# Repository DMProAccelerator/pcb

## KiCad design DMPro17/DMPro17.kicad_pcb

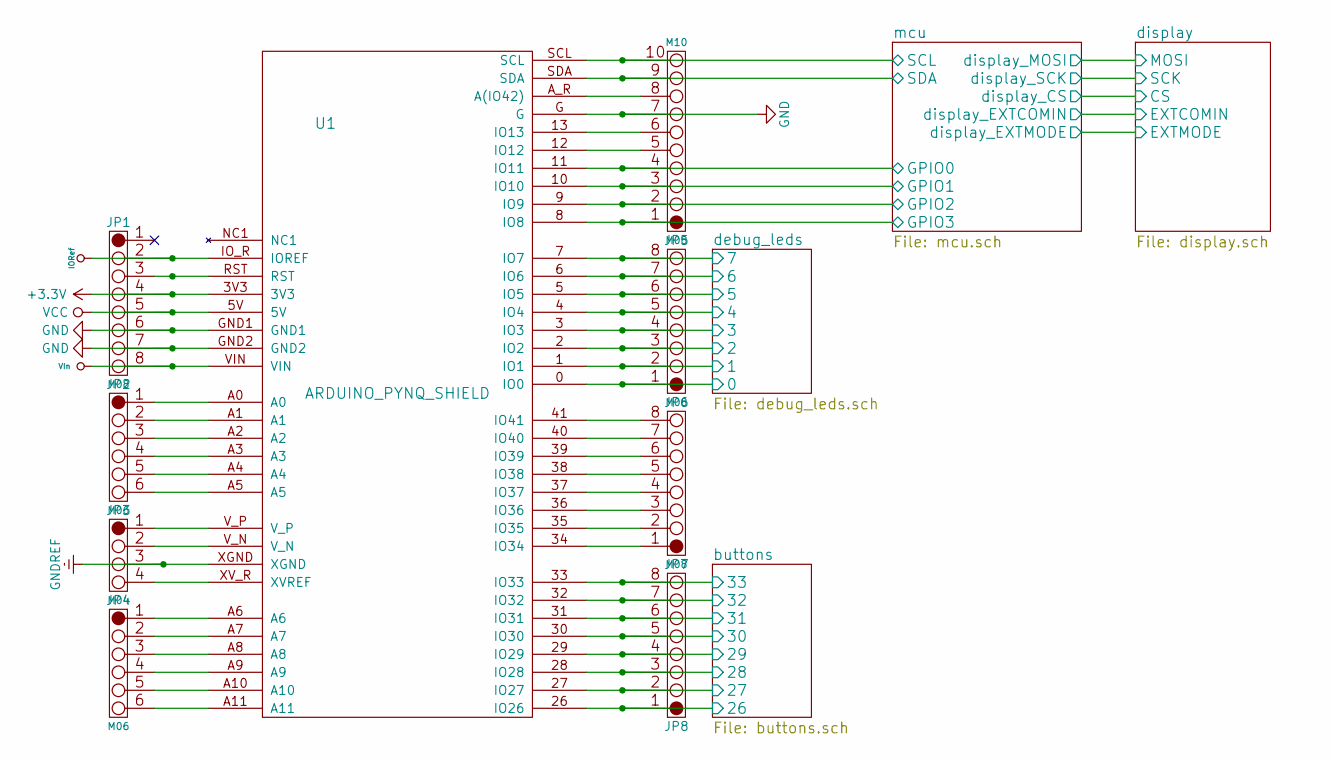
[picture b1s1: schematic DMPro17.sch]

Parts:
JP1, JP6, JP7, JP8: M08; 1X08
JP2, JP4: M06; 1X06
JP3: M04; 1X04
JP5: M10; 1X10
U1: ARDUINO_PYNQ_SHIELD

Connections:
+3V3: JP1.4, U1.3V3; also elsewhere on the board
/buttons/26: JP8.1, U1.26 (IO26); also elsewhere on the board
/buttons/27: JP8.2, U1.27 (IO27); also elsewhere on the board
/buttons/28: JP8.3, U1.28 (IO28); also elsewhere on the board
/buttons/29: JP8.4, U1.29 (IO29); also elsewhere on the board
/buttons/30: JP8.5, U1.30 (IO30); also elsewhere on the board
/buttons/31: JP8.6, U1.31 (IO31); also elsewhere on the board
/buttons/32: JP8.7, U1.32 (IO32); also elsewhere on the board
/buttons/33: JP8.8, U1.33 (IO33); also elsewhere on the board
/debug_leds/0: JP6.1, U1.0 (IO0); also elsewhere on the board
/debug_leds/1: JP6.2, U1.1 (IO1); also elsewhere on the board
/debug_leds/2: JP6.3, U1.2 (IO2); also elsewhere on the board
/debug_leds/3: JP6.4, U1.3 (IO3); also elsewhere on the board
/debug_leds/4: JP6.5, U1.4 (IO4); also elsewhere on the board
/debug_leds/5: JP6.6, U1.5 (IO5); also elsewhere on the board
/debug_leds/6: JP6.7, U1.6 (IO6); also elsewhere on the board
/debug_leds/7: JP6.8, U1.7 (IO7); also elsewhere on the board
/mcu/GPIO0: JP5.4, U1.11 (IO11); also elsewhere on the board
/mcu/GPIO1: JP5.3, U1.10 (IO10); also elsewhere on the board
/mcu/GPIO2: JP5.2, U1.9 (IO9); also elsewhere on the board
/mcu/GPIO3: JP5.1, U1.8 (IO8); also elsewhere on the board
/mcu/SCL: JP5.10, U1.SCL; also elsewhere on the board
/mcu/SDA: JP5.9, U1.SDA; also elsewhere on the board
GND: JP1.6, JP1.7, JP5.7, U1.G, U1.GND1, U1.GND2; also elsewhere on the board
GNDREF: JP3.3, U1.XGND
IORef: JP1.2, U1.IO_R (IOREF)
unnamed: JP1.3, U1.RST
unnamed: JP2.1, U1.A0
unnamed: JP2.2, U1.A1
unnamed: JP2.3, U1.A2
unnamed: JP2.4, U1.A3
unnamed: JP2.5, U1.A4
unnamed: JP2.6, U1.A5
unnamed: JP3.1, U1.V_P
unnamed: JP3.2, U1.V_N
unnamed: JP3.4, U1.XV_R (XVREF)
unnamed: JP4.1, U1.A6
unnamed: JP4.2, U1.A7
unnamed: JP4.3, U1.A8
unnamed: JP4.4, U1.A9
unnamed: JP4.5, U1.A10
unnamed: JP4.6, U1.A11
unnamed: JP5.5, U1.12 (IO12)
unnamed: JP5.6, U1.13 (IO13)
unnamed: JP5.8, U1.A_R (A(IO42))
unnamed: JP7.1, U1.34 (IO34)
unnamed: JP7.2, U1.35 (IO35)
unnamed: JP7.3, U1.36 (IO36)
unnamed: JP7.4, U1.37 (IO37)
unnamed: JP7.5, U1.38 (IO38)
unnamed: JP7.6, U1.39 (IO39)
unnamed: JP7.7, U1.40 (IO40)
unnamed: JP7.8, U1.41 (IO41)
VCC: JP1.5, U1.5V
VIn: JP1.8, U1.VIN

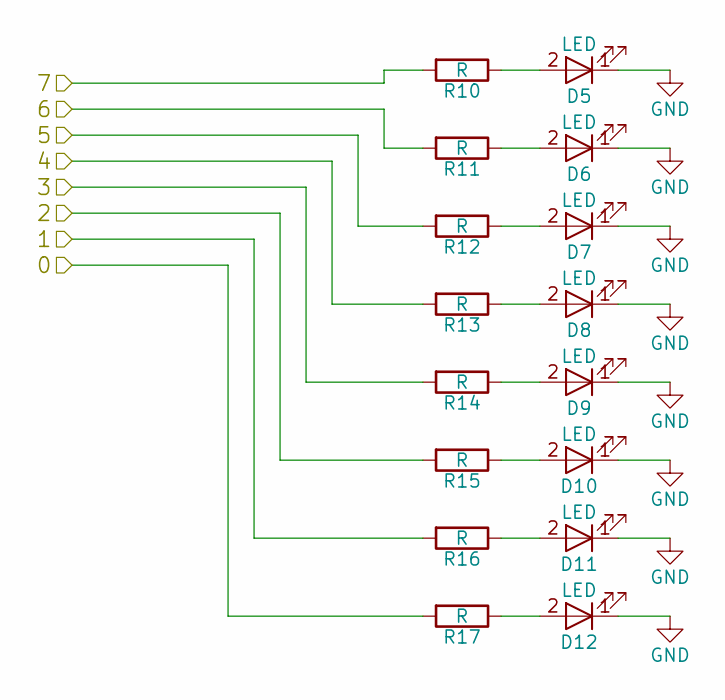
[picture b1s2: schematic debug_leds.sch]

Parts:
D5, D6, D7, D8, D9, D10, D11, D12: LED; LED_0603
R10, R11, R12, R13, R14, R15, R16, R17: R; R_0603

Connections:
/debug_leds/0: R17.2; also elsewhere on the board
/debug_leds/1: R16.2; also elsewhere on the board
/debug_leds/2: R15.2; also elsewhere on the board
/debug_leds/3: R14.2; also elsewhere on the board
/debug_leds/4: R13.2; also elsewhere on the board
/debug_leds/5: R12.2; also elsewhere on the board
/debug_leds/6: R11.2; also elsewhere on the board
/debug_leds/7: R10.2; also elsewhere on the board
GND: D5.1 (K), D6.1 (K), D7.1 (K), D8.1 (K), D9.1 (K), D10.1 (K), D11.1 (K), D12.1 (K); also elsewhere on the board
unnamed: D5.2 (A), R10.1
unnamed: D6.2 (A), R11.1
unnamed: D7.2 (A), R12.1
unnamed: D8.2 (A), R13.1
unnamed: D9.2 (A), R14.1
unnamed: D10.2 (A), R15.1
unnamed: D11.2 (A), R16.1
unnamed: D12.2 (A), R17.1

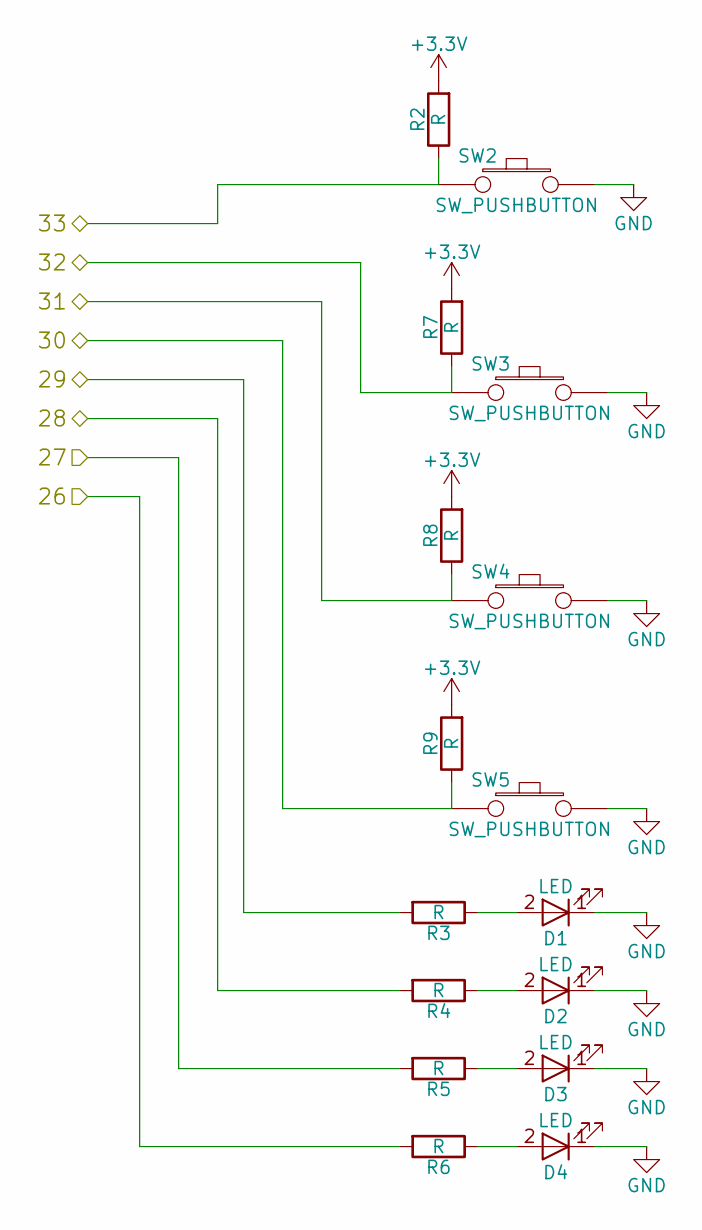
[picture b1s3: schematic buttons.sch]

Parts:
D1, D2, D3, D4: LED; LED_0603
R2, R3, R4, R5, R6, R7, R8, R9: R; R_0603
SW2, SW3, SW4, SW5: SW_PUSHBUTTON; SW_PUSHBUTTON_SMD

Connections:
+3V3: R2.2, R7.2, R8.2, R9.2; also elsewhere on the board
/buttons/26: R6.2; also elsewhere on the board
/buttons/27: R5.2; also elsewhere on the board
/buttons/28: R4.2; also elsewhere on the board
/buttons/29: R3.2; also elsewhere on the board
/buttons/30: R9.1, SW5.1; also elsewhere on the board
/buttons/31: R8.1, SW4.1; also elsewhere on the board
/buttons/32: R7.1, SW3.1; also elsewhere on the board
/buttons/33: R2.1, SW2.1; also elsewhere on the board
GND: D1.1 (K), D2.1 (K), D3.1 (K), D4.1 (K), SW2.2, SW3.2, SW4.2, SW5.2; also elsewhere on the board
unnamed: D1.2 (A), R3.1
unnamed: D2.2 (A), R4.1
unnamed: D3.2 (A), R5.1
unnamed: D4.2 (A), R6.1

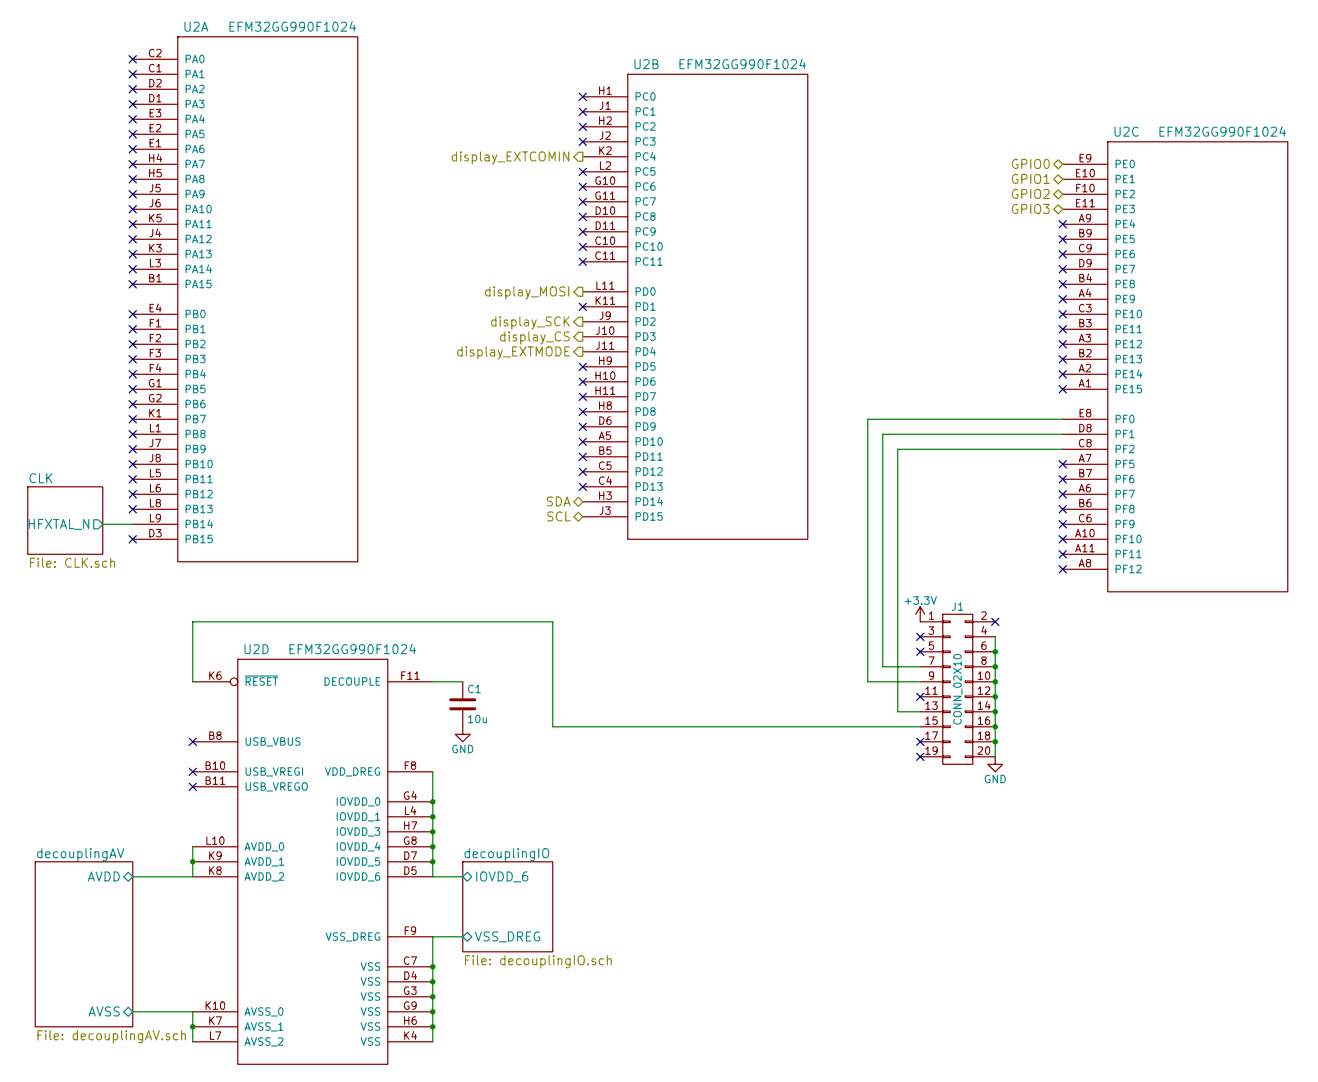
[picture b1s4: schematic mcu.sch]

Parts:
C1: 10u; C_0603
J1: CONN_02X10; Multicomp_MC9A12-2034_2x10x2.54mm_Straight
U2: EFM32GG990F1024; EFM32_BGA112

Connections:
+3V3: J1.1, U2.D5 (IOVDD_6), U2.D7 (IOVDD_5), U2.F8 (VDD_DREG), U2.G4 (IOVDD_0), U2.G8 (IOVDD_4), U2.H7 (IOVDD_3), U2.L4 (IOVDD_1); also elsewhere on the board
/display/CS: U2.J10 (PD3); also elsewhere on the board
/display/EXTCOMIN: U2.K2 (PC4); also elsewhere on the board
/display/EXTMODE: U2.J11 (PD4); also elsewhere on the board
/display/MOSI: U2.L11 (PD0); also elsewhere on the board
/display/SCK: U2.J9 (PD2); also elsewhere on the board
/mcu/CLK/HFXTAL_N: U2.L9 (PB14); also elsewhere on the board
/mcu/GPIO0: U2.E9 (PE0); also elsewhere on the board
/mcu/GPIO1: U2.E10 (PE1); also elsewhere on the board
/mcu/GPIO2: U2.F10 (PE2); also elsewhere on the board
/mcu/GPIO3: U2.E11 (PE3); also elsewhere on the board
/mcu/SCL: U2.J3 (PD15); also elsewhere on the board
/mcu/SDA: U2.H3 (PD14); also elsewhere on the board
/mcu/decouplingAV/AVDD: U2.K8 (AVDD_2), U2.K9 (AVDD_1), U2.L10 (AVDD_0); also elsewhere on the board
GND: C1.2, J1.4, J1.6, J1.8, J1.10, J1.12, J1.14, J1.16, J1.18, J1.20, U2.C7 (VSS), U2.D4 (VSS), U2.F9 (VSS_DREG), U2.G3 (VSS), U2.G9 (VSS), U2.H6 (VSS), U2.K4 (VSS), U2.K7 (AVSS_1), U2.K10 (AVSS_0), U2.L7 (AVSS_2); also elsewhere on the board
unnamed: C1.1, U2.F11 (DECOUPLE)
unnamed: J1.7, U2.D8 (PF1)
unnamed: J1.9, U2.E8 (PF0)
unnamed: J1.13, U2.C8 (PF2)
unnamed: J1.15, U2.K6 (~RESET~)

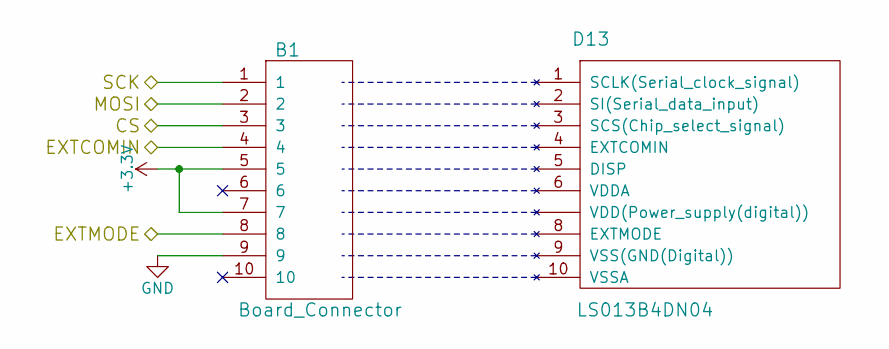
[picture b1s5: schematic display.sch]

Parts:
B1: Board_Connector
D13: LS013B4DN04

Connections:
+3V3: B1.5, B1.7; also elsewhere on the board
/display/CS: B1.3; also elsewhere on the board
/display/EXTCOMIN: B1.4; also elsewhere on the board
/display/EXTMODE: B1.8; also elsewhere on the board
/display/MOSI: B1.2; also elsewhere on the board
/display/SCK: B1.1; also elsewhere on the board
GND: B1.9; also elsewhere on the board

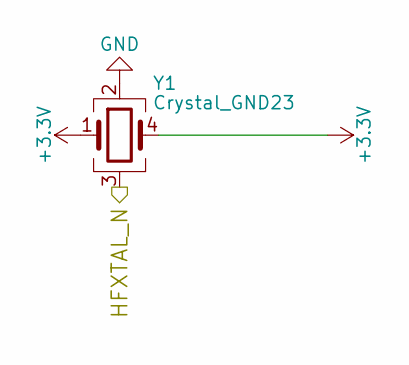
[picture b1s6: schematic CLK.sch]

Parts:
Y1: Crystal_GND23; Crystal_SMD_3225-4pin_3.2x2.5mm

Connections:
+3V3: Y1.1, Y1.4; also elsewhere on the board
/mcu/CLK/HFXTAL_N: Y1.3; also elsewhere on the board
GND: Y1.2; also elsewhere on the board

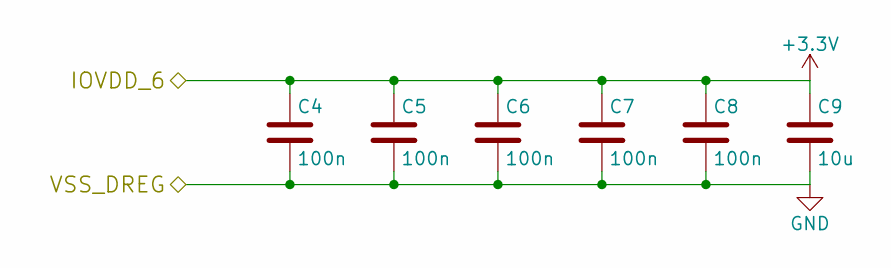
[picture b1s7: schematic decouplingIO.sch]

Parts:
C4, C5, C6, C7, C8: 100n; C_0603
C9: 10u; C_0603

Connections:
+3V3: C4.1, C5.1, C6.1, C7.1, C8.1, C9.1; also elsewhere on the board
GND: C4.2, C5.2, C6.2, C7.2, C8.2, C9.2; also elsewhere on the board

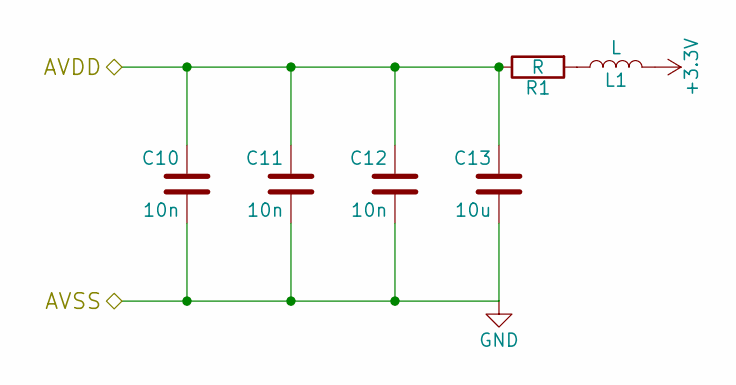
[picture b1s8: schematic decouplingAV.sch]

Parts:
C10, C11, C12: 10n; C_0603
C13: 10u; C_0603
L1: L; L_0603
R1: R; R_0603

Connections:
+3V3: L1.1; also elsewhere on the board
/mcu/decouplingAV/AVDD: C10.1, C11.1, C12.1, C13.1, R1.1; also elsewhere on the board
GND: C10.2, C11.2, C12.2, C13.2; also elsewhere on the board
unnamed: L1.2, R1.2

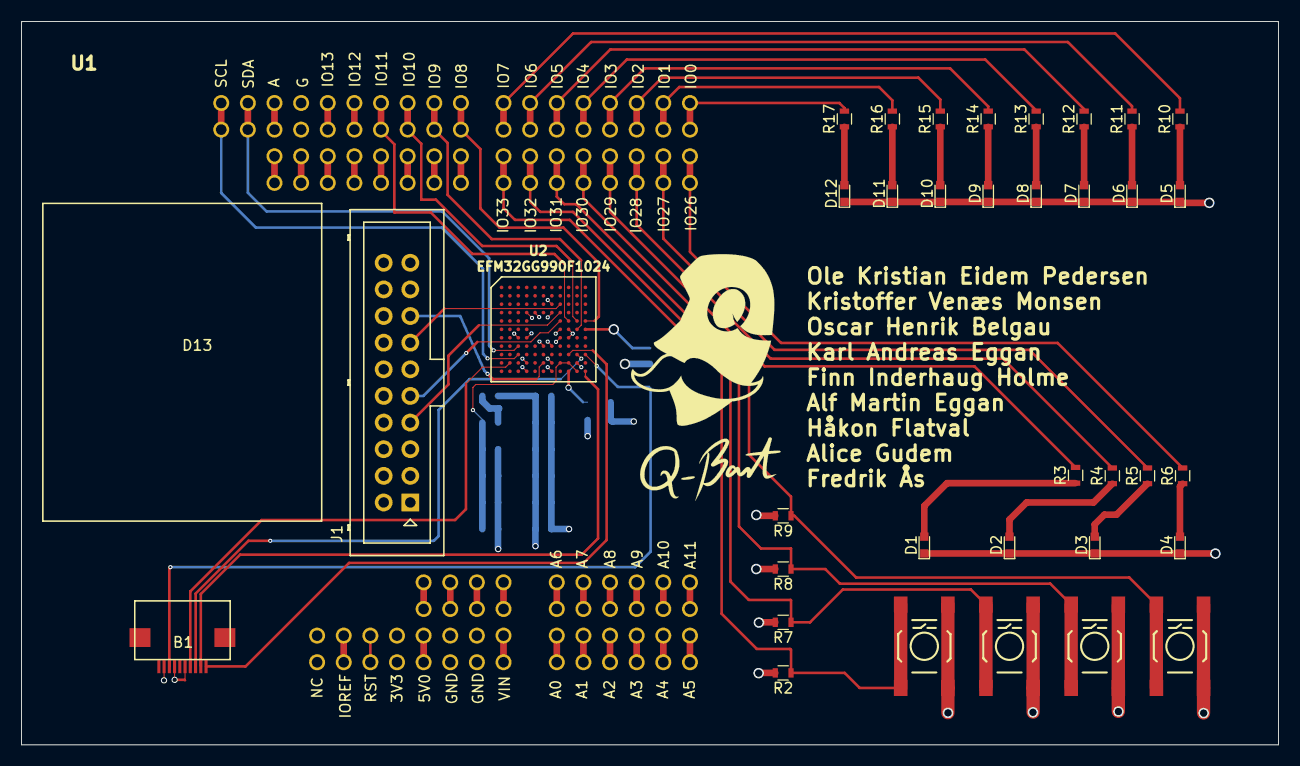
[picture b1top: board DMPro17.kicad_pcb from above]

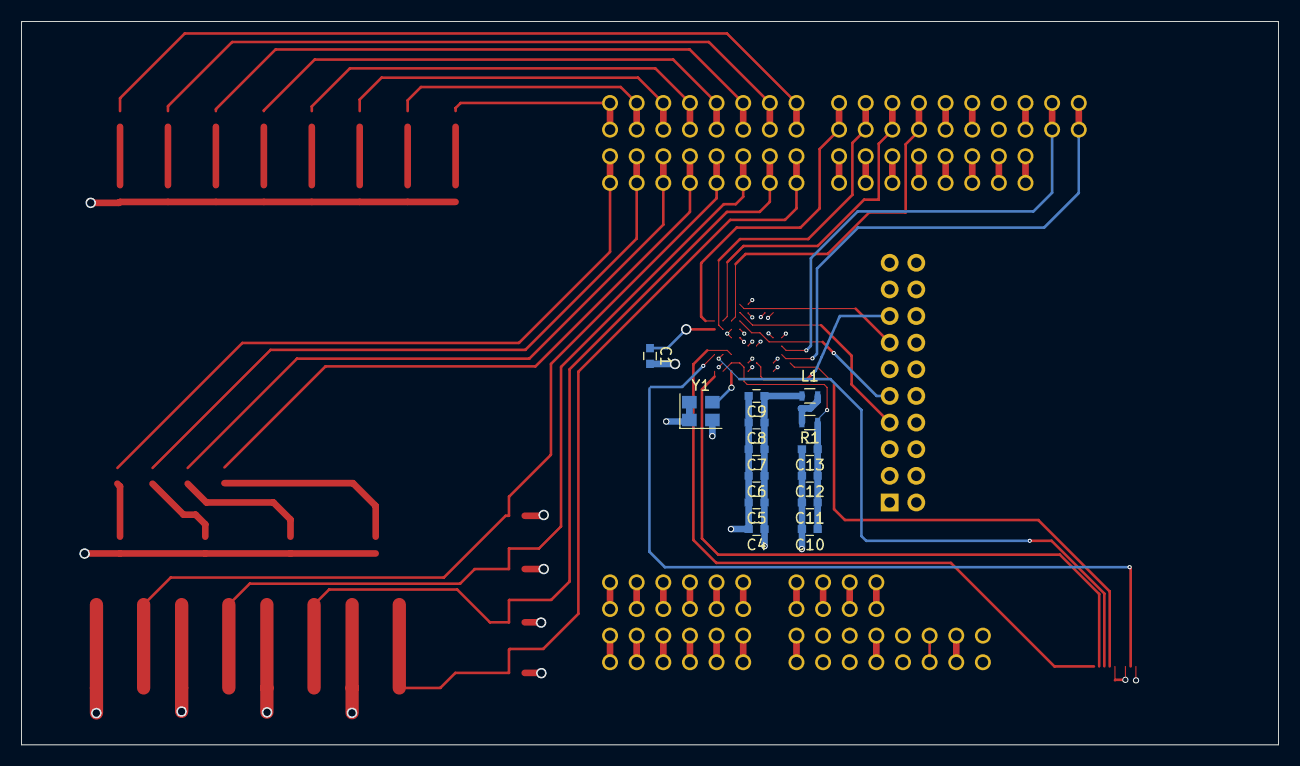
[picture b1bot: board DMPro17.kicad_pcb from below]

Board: 4 copper layers, 119.9 x 69.0 mm, 59 parts (14 on the bottom side), 80 nets.

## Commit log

2017-10-05 Added documentation for components
2017-10-05 PCB files
2017-10-05 Bill of Materials
2017-10-10 Added new gerber files
2017-10-12 Added source code
2017-10-26 Added skeleton
2017-10-27 Added to skeleton
2017-11-17 cleaning
